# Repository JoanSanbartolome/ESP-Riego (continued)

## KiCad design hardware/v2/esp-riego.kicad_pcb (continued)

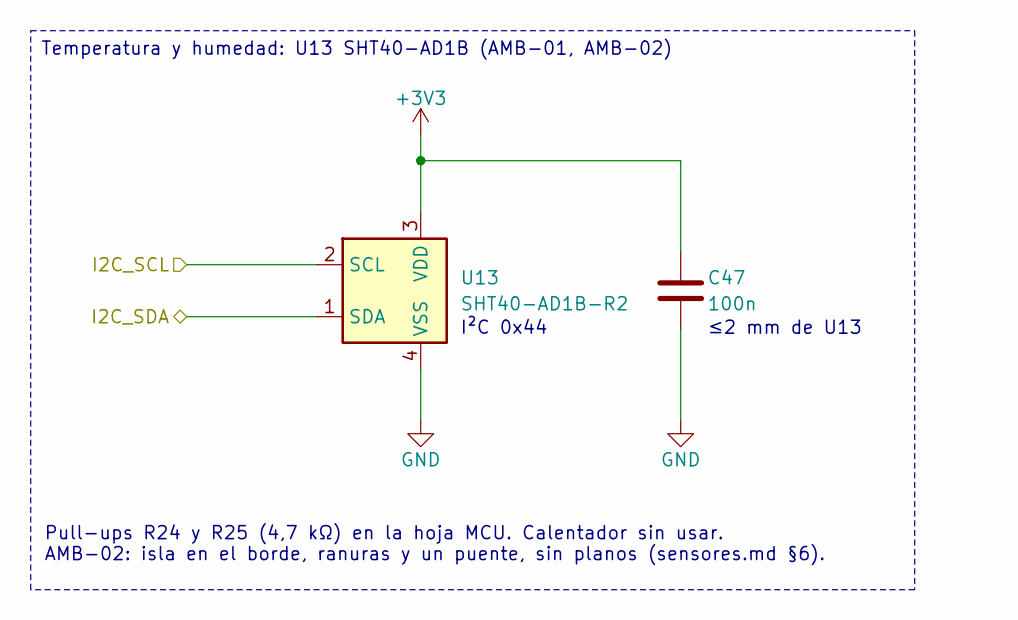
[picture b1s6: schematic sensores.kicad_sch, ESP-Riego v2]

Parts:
C47: 100n; C_0603_1608Metric; MPN CC0603KRX7R9BB104; LCSC Part# C14663
U13: SHT40-AD1B-R2; Sensirion_DFN-4_1.5x1.5mm_P0.8mm_SHT4x_NoCentralPad; MPN SHT40-AD1B-R2; LCSC Part# C2909890

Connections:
+3V3: C47.1, U13.3 (VDD); also elsewhere on the board
/I2C_SCL: U13.2 (SCL); also elsewhere on the board
/I2C_SDA: U13.1 (SDA); also elsewhere on the board
GND: C47.2, U13.4 (VSS); also elsewhere on the board

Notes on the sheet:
I²C 0x44
≤2 mm de U13
Pull-ups R24 y R25 (4,7 kΩ) en la hoja MCU. Calentador sin usar. AMB-02: isla en el borde, ranuras y un puente, sin planos (sensores.md §6).
Temperatura y humedad: U13 SHT40-AD1B (AMB-01, AMB-02)

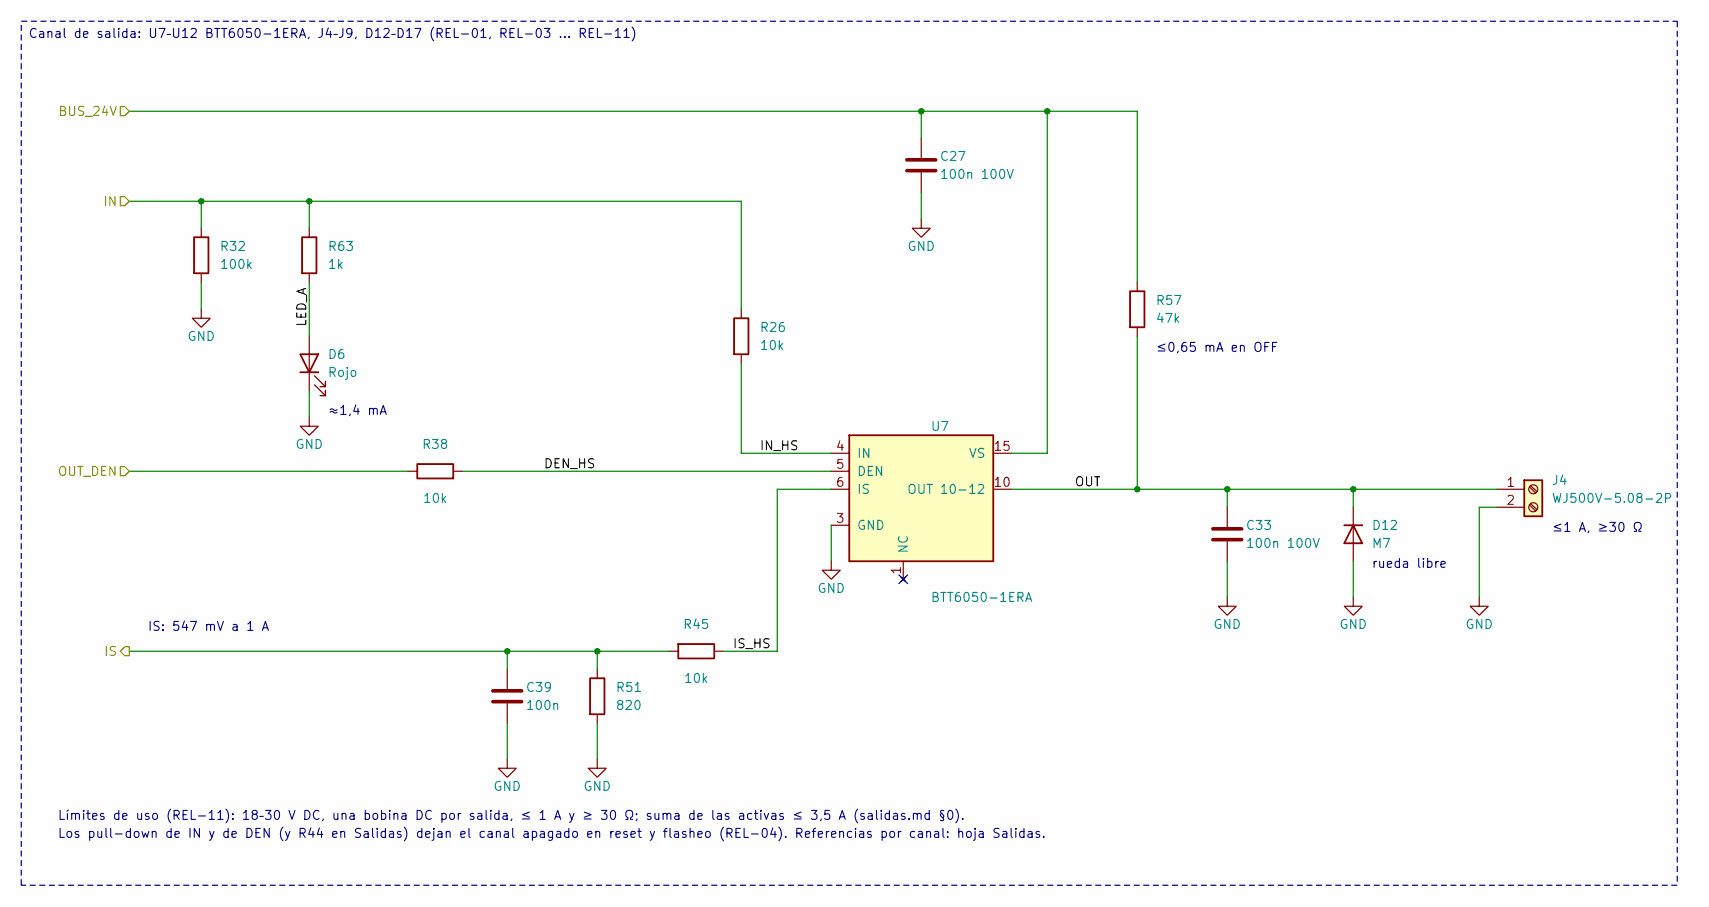
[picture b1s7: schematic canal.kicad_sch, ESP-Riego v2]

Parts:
C27, C33: 100n 100V; C_0805_2012Metric; MPN CL21B104KCFNNNE; LCSC Part# C28233
C39: 100n; C_0603_1608Metric; MPN CC0603KRX7R9BB104; LCSC Part# C14663
D6: Rojo; LED_0603_1608Metric; MPN KT-0603R; LCSC Part# C2286
D12: M7; D_SMA; MPN M7; LCSC Part# C95872
J4: WJ500V-5.08-2P; TerminalBlock_Kangnex_WJ500V-5.08-2P_1x02_P5.08mm_Horizontal; MPN WJ500V-5.08-2P; LCSC Part# C8465
R26, R38: 10k; R_0603_1608Metric; MPN 0603WAF1002T5E; LCSC Part# C25804
R32: 100k; R_0603_1608Metric; MPN 0603WAF1003T5E; LCSC Part# C25803
R45: 10k; R_1206_3216Metric; MPN 1206W4F1002T5E; LCSC Part# C17902
R51: 820; R_0603_1608Metric; MPN 0603WAF8200T5E; LCSC Part# C23253
R57: 47k; R_0805_2012Metric; MPN 0805W8F4702T5E; LCSC Part# C17713
R63: 1k; R_0603_1608Metric; MPN 0603WAF1001T5E; LCSC Part# C21190
U7: BTT6050-1ERA; Infineon_PG-TDSO-14_8.65x3.9mm_P1.27mm_EP2.65x6.4mm; MPN BTT6050-1ERA; LCSC Part# C534868

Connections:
/BUS_24V: C27.1, R57.1, U7.15 (VS); also elsewhere on the board
/IN1: R26.1, R32.1, R63.1; also elsewhere on the board
/IS1: C39.1, R45.2, R51.1; also elsewhere on the board
/OUT_DEN: R38.1; also elsewhere on the board
/Salidas/Canal1/DEN_HS: R38.2, U7.5 (DEN)
/Salidas/Canal1/IN_HS: R26.2, U7.4 (IN)
/Salidas/Canal1/IS_HS: R45.1, U7.6 (IS)
/Salidas/Canal1/LED_A: D6.2 (A), R63.2
/Salidas/Canal1/OUT: C33.1, D12.1 (K), J4.1, R57.2, U7.10 (OUT 10-12), U7.11 (OUT 10-12), U7.12 (OUT 10-12)
GND: C27.2, C33.2, C39.2, D6.1 (K), D12.2 (A), J4.2, R32.2, R51.2, U7.3 (GND); also elsewhere on the board

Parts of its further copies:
C28, C29, C30, C31, C32, C34, C35, C36, C37, C38: 100n 100V; C_0805_2012Metric; MPN CL21B104KCFNNNE; LCSC Part# C28233
C40, C41, C42, C43, C44: 100n; C_0603_1608Metric; MPN CC0603KRX7R9BB104; LCSC Part# C14663
D7, D8, D9, D10, D11: Rojo; LED_0603_1608Metric; MPN KT-0603R; LCSC Part# C2286
D13, D14, D15, D16, D17: M7; D_SMA; MPN M7; LCSC Part# C95872
J5, J6, J7, J8, J9: WJ500V-5.08-2P; TerminalBlock_Kangnex_WJ500V-5.08-2P_1x02_P5.08mm_Horizontal; MPN WJ500V-5.08-2P; LCSC Part# C8465
R27, R28, R29, R30, R31, R39, R40, R41, R42, R43: 10k; R_0603_1608Metric; MPN 0603WAF1002T5E; LCSC Part# C25804
R33, R34, R35, R36, R37: 100k; R_0603_1608Metric; MPN 0603WAF1003T5E; LCSC Part# C25803
R46, R47, R48, R49, R50: 10k; R_1206_3216Metric; MPN 1206W4F1002T5E; LCSC Part# C17902
R52, R53, R54, R55, R56: 820; R_0603_1608Metric; MPN 0603WAF8200T5E; LCSC Part# C23253
R58, R59, R60, R61, R62: 47k; R_0805_2012Metric; MPN 0805W8F4702T5E; LCSC Part# C17713
R64, R65, R66, R67, R68: 1k; R_0603_1608Metric; MPN 0603WAF1001T5E; LCSC Part# C21190
U8, U9, U10, U11, U12: BTT6050-1ERA; Infineon_PG-TDSO-14_8.65x3.9mm_P1.27mm_EP2.65x6.4mm; MPN BTT6050-1ERA; LCSC Part# C534868

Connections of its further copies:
/BUS_24V: C28.1, C29.1, C30.1, C31.1, C32.1, R58.1, R59.1, R60.1, R61.1, R62.1, U8.15 (VS), U9.15 (VS), U10.15 (VS), U11.15 (VS), U12.15 (VS); also elsewhere on the board
/IN2: R27.1, R33.1, R64.1; also elsewhere on the board
/IN3: R28.1, R34.1, R65.1; also elsewhere on the board
/IN4: R29.1, R35.1, R66.1; also elsewhere on the board
/IN5: R30.1, R36.1, R67.1; also elsewhere on the board
/IN6: R31.1, R37.1, R68.1; also elsewhere on the board
/IS2: C40.1, R46.2, R52.1; also elsewhere on the board
/IS3: C41.1, R47.2, R53.1; also elsewhere on the board
/IS4: C42.1, R48.2, R54.1; also elsewhere on the board
/IS5: C43.1, R49.2, R55.1; also elsewhere on the board
/IS6: C44.1, R50.2, R56.1; also elsewhere on the board
/OUT_DEN: R39.1, R40.1, R41.1, R42.1, R43.1; also elsewhere on the board
/Salidas/Canal2/DEN_HS: R39.2, U8.5 (DEN)
/Salidas/Canal2/IN_HS: R27.2, U8.4 (IN)
/Salidas/Canal2/IS_HS: R46.1, U8.6 (IS)
/Salidas/Canal2/LED_A: D7.2 (A), R64.2
/Salidas/Canal2/OUT: C34.1, D13.1 (K), J5.1, R58.2, U8.10 (OUT 10-12), U8.11 (OUT 10-12), U8.12 (OUT 10-12)
/Salidas/Canal3/DEN_HS: R40.2, U9.5 (DEN)
/Salidas/Canal3/IN_HS: R28.2, U9.4 (IN)
/Salidas/Canal3/IS_HS: R47.1, U9.6 (IS)
/Salidas/Canal3/LED_A: D8.2 (A), R65.2
/Salidas/Canal3/OUT: C35.1, D14.1 (K), J6.1, R59.2, U9.10 (OUT 10-12), U9.11 (OUT 10-12), U9.12 (OUT 10-12)
/Salidas/Canal4/DEN_HS: R41.2, U10.5 (DEN)
/Salidas/Canal4/IN_HS: R29.2, U10.4 (IN)
/Salidas/Canal4/IS_HS: R48.1, U10.6 (IS)
/Salidas/Canal4/LED_A: D9.2 (A), R66.2
/Salidas/Canal4/OUT: C36.1, D15.1 (K), J7.1, R60.2, U10.10 (OUT 10-12), U10.11 (OUT 10-12), U10.12 (OUT 10-12)
/Salidas/Canal5/DEN_HS: R42.2, U11.5 (DEN)
/Salidas/Canal5/IN_HS: R30.2, U11.4 (IN)
/Salidas/Canal5/IS_HS: R49.1, U11.6 (IS)
/Salidas/Canal5/LED_A: D10.2 (A), R67.2
/Salidas/Canal5/OUT: C37.1, D16.1 (K), J8.1, R61.2, U11.10 (OUT 10-12), U11.11 (OUT 10-12), U11.12 (OUT 10-12)
/Salidas/Canal6/DEN_HS: R43.2, U12.5 (DEN)
/Salidas/Canal6/IN_HS: R31.2, U12.4 (IN)
/Salidas/Canal6/IS_HS: R50.1, U12.6 (IS)
/Salidas/Canal6/LED_A: D11.2 (A), R68.2
/Salidas/Canal6/OUT: C38.1, D17.1 (K), J9.1, R62.2, U12.10 (OUT 10-12), U12.11 (OUT 10-12), U12.12 (OUT 10-12)
GND: C28.2, C29.2, C30.2, C31.2, C32.2, C34.2, C35.2, C36.2, C37.2, C38.2, C40.2, C41.2, C42.2, C43.2, C44.2, D7.1 (K), D8.1 (K), D9.1 (K), D10.1 (K), D11.1 (K), D13.2 (A), D14.2 (A), D15.2 (A), D16.2 (A), D17.2 (A), J5.2, J6.2, J7.2, J8.2, J9.2, R33.2, R34.2, R35.2, R36.2, R37.2, R52.2, R53.2, R54.2, R55.2, R56.2, U8.3 (GND), U9.3 (GND), U10.3 (GND), U11.3 (GND), U12.3 (GND); also elsewhere on the board

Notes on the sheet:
≈1,4 mA
≤0,65 mA en OFF
rueda libre
≤1 A, ≥30 Ω
IS: 547 mV a 1 A
Límites de uso (REL-11): 18–30 V DC, una bobina DC por salida, ≤ 1 A y ≥ 30 Ω; suma de las activas ≤ 3,5 A (salidas.md §0).
Los pull-down de IN y de DEN (y R44 en Salidas) dejan el canal apagado en reset y flasheo (REL-04). Referencias por canal: hoja Salidas.
Canal de salida: U7–U12 BTT6050-1ERA, J4–J9, D12–D17 (REL-01, REL-03 … REL-11)

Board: 2 copper layers, 197 parts (0 on the bottom side), 101 nets, no tracks yet.

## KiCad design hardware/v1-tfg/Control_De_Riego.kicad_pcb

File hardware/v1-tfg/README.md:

# v1-tfg — proyecto del TFG en formato KiCad 10

Copia de la v1 (`Control_De_Riego`) del TFG de Joan San Bartolomé Ferri. **El diseño no se ha tocado**: solo se han cambiado las rutas de librería, la hoja de dibujo, los modelos 3D y el formato de archivo (SPEC-0009). Los hallazgos H1–H12 de `docs/01-analisis-v1.md` siguen presentes.

## Origen

`C:\Users\josan\proyectos\TFG\KiCad_PCB\Control_De_Riego` (carpeta de trabajo, igual que `PCB_FINAL.rar`) y `C:\Users\josan\proyectos\TFG\Llibreries_Kicad`. Solo se leyó del TFG; su huella (`gestion/tfg-manifiesto.json`) sigue intacta.

## Qué se copió

- Proyecto: `Control_De_Riego.kicad_pro`, `.kicad_sch` (raíz), `allimentacion`, `conectores`, `modulo_reles`, `wemos_s2mini` (`.kicad_sch`) y `Control_De_Riego.kicad_pcb`.
- `referencia/Panel_Control.kicad_sch`: hoja fuera de la jerarquía (H9), solo como referencia. Está guardada también en formato KiCad 10.
- Librerías propias en `../libraries/` con los mismos nicknames que las tablas originales (ver abajo).

No se copió: `Control_De_Riego-backups/`, `fp-info-cache`, `.kicad_prl`, `.step` del proyecto, `untitled.kicad_sch` (duplicado del Wemos) ni los `.rar`.

## Librerías (`../libraries/`)

| Nickname | Tipo | Archivo | Origen |
|---|---|---|---|
| `PS2705-1-F3-A`, `BC817-25-7-F`, `1548129`, `PRT-10811` | símbolos | `<nick>.kicad_sym` | `.lib` + `.dcm` de la librería del TFG, convertidos con `kicad-cli sym upgrade` |
| `Wemos s2 mini` | símbolo | `Wemos s2 mini.kicad_sym` | JSON de EasyEDA (`SCHLIB_WEMOS-S2-MINI-…json`) convertido tal cual con `kicad-cli sym upgrade -o` (SPEC-0010) |
| `PS2705`, `BC817-25-7`, `PRT10811`, `KiCad`, `PhoenixTerminal`, `SMMS0530-150M` | huellas | `<nick>.pretty` | `.kicad_mod` de la librería del TFG, actualizados con `kicad-cli fp upgrade` (`KiCad` = `1548129`; `SMMS0530-150M` incluye también `IND-SMD_L5.5-W5.2`) |
| `Wemos s2 mini` | huella | `Wemos s2 mini.pretty` | JSON de EasyEDA (`PCBLIB_WEMOS-S2-MINI_…json`) convertido tal cual con `kicad-cli fp upgrade -o` (SPEC-0010); no lleva modelo 3D |
| `DC-Jack` | huella | `DC-Jack.pretty/DC-IN-TH_XDJK-0051-025` | JSON de EasyEDA convertido tal cual con `kicad-cli fp upgrade -o` (SPEC-0010). Tiene 3 pads; el pad 3 es `custom` con polígono de 3,56 × 1,60 mm y taladro oblongo de 3×1 mm, equivalente a los pads 1 y 2 girados 90° (no es un artefacto). No se usa en la PCB (el jack real es `Connector_BarrelJack`) |

También `Cajetin_Kicad.kicad_wks` (hoja de dibujo) y `3d/` (`TLP185.step`, `Transistor.IGS`, `PSMT3012.STEP`, `Wemos S2 Mini V1.0.0.step`).

## Cambios de ruta

- `sym-lib-table` y `fp-lib-table`: reescritas con `${KIPRJMOD}/../libraries/...` y tipo `KiCad` (antes `Legacy` y EasyEDA, con rutas `G:/…`).
- `Control_De_Riego.kicad_pro`: `page_layout_descr_file` (dos apariciones) a `${KIPRJMOD}/../libraries/Cajetin_Kicad.kicad_wks`; `export… svg` (ruta `C:/Users/josan/Desktop/…`, último directorio de exportación) vaciado.
- `Control_De_Riego.kicad_pcb`: 10 modelos 3D con ruta `G:/…` a `${KIPRJMOD}/../libraries/3d/<archivo>` (4× TLP185, 4× Transistor, 1× PSMT3012, 1× Wemos); 43 modelos `${KICAD9_3DMODEL_DIR}` a `${KICAD10_3DMODEL_DIR}` (normalización a la variable de KiCad 10; la antigua también resuelve, así que el cambio es inocuo).
- Modelos 3D: 42 de los 53 modelos de la PCB apuntan a un `.wrl`, y KiCad 10.0.6 no instala ningún `.wrl` (solo `.step`), así que esos modelos no se ven en el visor 3D ni en el STEP (`Could not add 3D model`). Viene de la v1; se corrige en la copia de trabajo de la v2 (`.wrl` a `.step`).
- Esquemas y PCB: `kicad-cli sch|pcb upgrade --force` (esquema `20260306`, PCB `20260206`).

## Verificación

`python herramientas/verificar.py hardware/v1-tfg`:

| | Antes (copia sin migrar) | Después |
|---|---|---|
| ERC | 1 (`pin_to_pin`) | 1 (`pin_to_pin`) |
| DRC | 1 error `starved_thermal`, 39 `lib_footprint_mismatch`, 0 sin conectar | 1 error `starved_thermal`, 39 `lib_footprint_mismatch`, 0 sin conectar (40 en total, como antes) |
| Paridad | 77 (61 `LCSC Part#`, 10 `net_conflict`, 6 huellas) | 77 (igual) |

Tras SPEC-0010 el DRC coincide con la copia sin migrar: la huella `Wemos s2 mini` de la librería es la conversión del JSON de EasyEDA, igual que en el TFG, y vuelve a no coincidir con la copia de U1 en la PCB (`lib_footprint_mismatch`). Con la copia embebida en la PCB (SPEC-0009) el DRC era 39. Netlist (61 componentes, 70 redes), posiciones, pistas (262), vías (36) y zonas (3) son idénticas antes y después. Detalle en `gestion/logs/SPEC-0009/01-jr-conformidad.md`.

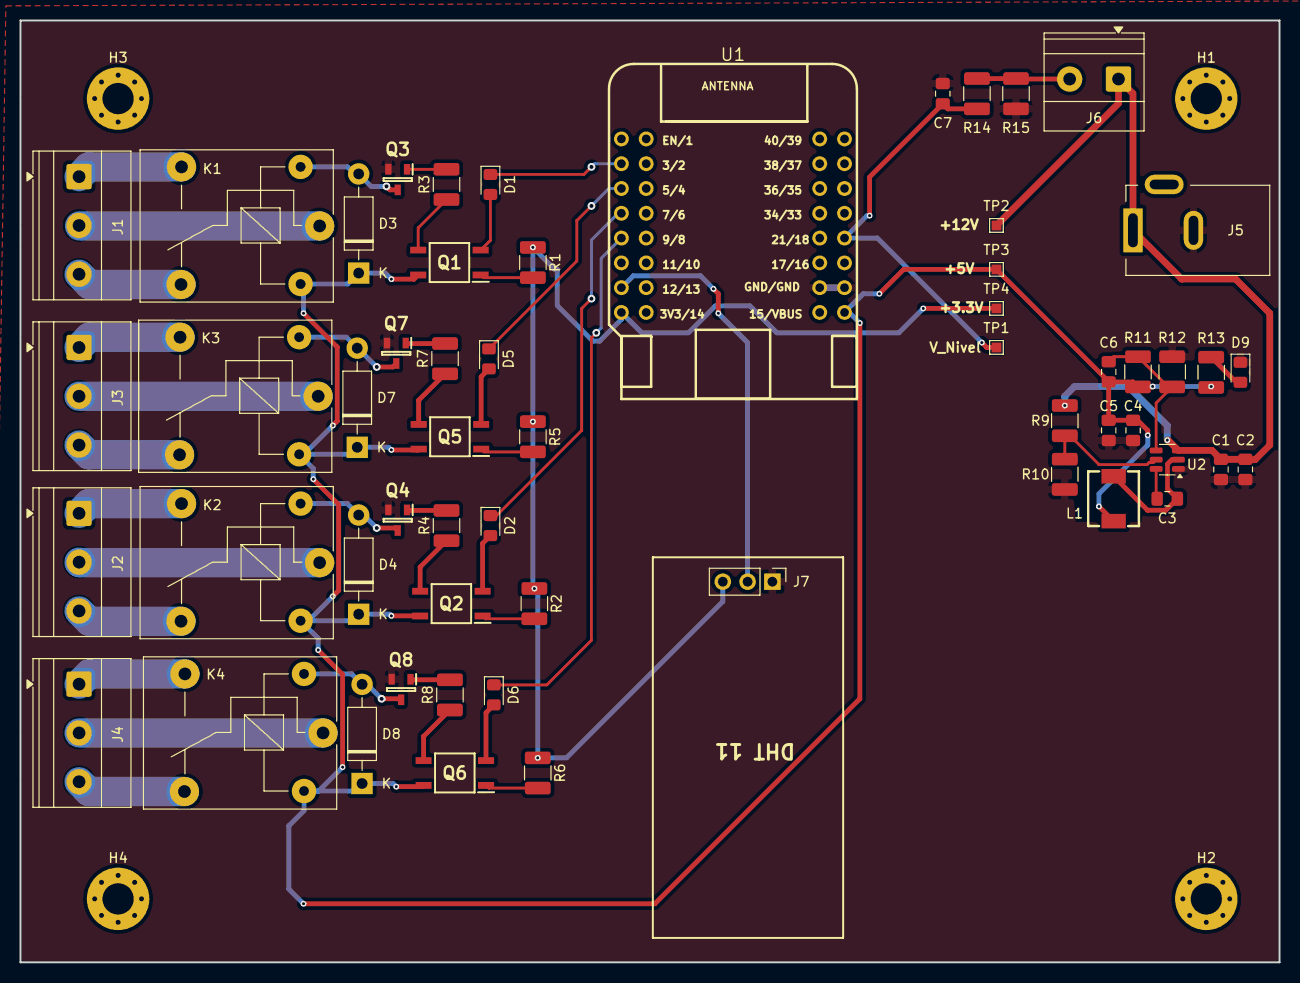
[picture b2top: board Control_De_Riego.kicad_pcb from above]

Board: 2 copper layers, 129.0 x 96.5 mm, 61 parts (0 on the bottom side), 48 nets.

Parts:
C1: 10uF; C_0805_2012Metric_Pad1.18x1.45mm_HandSolder
C2, C3, C7: 100nF; C_0805_2012Metric_Pad1.18x1.45mm_HandSolder
C4, C5: 22uF; C_0805_2012Metric_Pad1.18x1.45mm_HandSolder
C6: 68pF; C_0805_2012Metric_Pad1.18x1.45mm_HandSolder
D1, D2, D5, D6: Red; LED_0805_2012Metric_Pad1.15x1.40mm_HandSolder
D3, D4, D7, D8: 1N4007; D_DO-41_SOD81_P10.16mm_Horizontal
D9: Green; LED_0805_2012Metric_Pad1.15x1.40mm_HandSolder
H1, H2, H3, H4: MountingHole; MountingHole_3.2mm_M3_Pad_Via
J1: Conector Rele 1; TerminalBlock_Phoenix_MKDS-1,5-3_1x03_P5.00mm_Horizontal
J2: Conector Rele 3; TerminalBlock_Phoenix_MKDS-1,5-3_1x03_P5.00mm_Horizontal
J3: Conector Rele 2; TerminalBlock_Phoenix_MKDS-1,5-3_1x03_P5.00mm_Horizontal
J4: Conector Rele 4; TerminalBlock_Phoenix_MKDS-1,5-3_1x03_P5.00mm_Horizontal
J5: DC Jack; BarrelJack_Kycon_KLDX-0202-xC_Horizontal
J6: Conn_01x02; TerminalBlock_Phoenix_MKDS-1,5-2_1x02_P5.00mm_Horizontal
J7: Conn_01x03; PinHeader_1x03_P2.54mm_Vertical
K1, K2, K3, K4: SANYOU_SRD_Form_C; Relay_SPDT_SANYOU_SRD_Series_Form_C
L1: 22uH; IND-SMD_L5.5-W5.2
Q1, Q2, Q5, Q6: PS2705-1-F3-A; SOP254P700X230-4N
Q3, Q4, Q7, Q8: BC817-25-7-F; SOT96P240X110-3N
R1, R2, R5, R6: 50; R_1210_3225Metric_Pad1.30x2.65mm_HandSolder
R3, R4, R7, R8: 1k; R_1210_3225Metric_Pad1.30x2.65mm_HandSolder
R9, R14: 270k; R_1210_3225Metric_Pad1.30x2.65mm_HandSolder
R10: 33k; R_1210_3225Metric_Pad1.30x2.65mm_HandSolder
R11: 100k; R_1210_3225Metric_Pad1.30x2.65mm_HandSolder
R12: 13k; R_1210_3225Metric_Pad1.30x2.65mm_HandSolder
R13: 180; R_1210_3225Metric_Pad1.30x2.65mm_HandSolder
R15: 150; R_1210_3225Metric_Pad1.30x2.65mm_HandSolder
TP1, TP2, TP3, TP4: TestPoint; TestPoint_Pad_1.0x1.0mm
U1: WEMOS-S2-MINI (ESP32-S2FN4R2); WEMOS-S2-MINI
U2: TPS54202DDC; SOT-23-6

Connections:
+3.3V: J7.3, R1.1, R2.1, R5.1, R6.1, TP4.1, U1.15 (3V3)
+5V: C4.1, C5.1, C6.1, D3.1 (K), D4.1 (K), D7.1 (K), D8.1 (K), K1.5, K2.5, K3.5, K4.5, L1.2, Q1.4 (C), Q2.4 (C), Q5.4 (C), Q6.4 (C), R11.1, R13.1, TP3.1, U1.18 (VBUS)
+12V: C1.1, C2.1, J5.1, J6.1, R9.2, TP2.1, U2.3 (VIN)
/Modulo_reles/IN_REL1: J1.2, K1.1
/Modulo_reles/IN_REL2: J3.2, K3.1
/Modulo_reles/IN_REL3: J2.2, K2.1
/Modulo_reles/IN_REL4: J4.2, K4.1
/Modulo_reles/NC_REL1: J1.3, K1.4
/Modulo_reles/NC_REL2: J3.3, K3.4
/Modulo_reles/NC_REL3: J2.3, K2.4
/Modulo_reles/NC_REL4: J4.3, K4.4
/Modulo_reles/NO_REL1: J1.1, K1.3
/Modulo_reles/NO_REL2: J3.1, K3.3
/Modulo_reles/NO_REL3: J2.1, K2.3
/Modulo_reles/NO_REL4: J4.1, K4.3
GND: C1.2, C2.2, C4.2, C5.2, C7.2, D9.1 (K), J5.2, J7.1, Q3.2, Q4.2, Q7.2, Q8.2, R10.2, R12.1, R15.2, U1.19 (GND), U1.20 (GND), U2.1 (GND)
unnamed: D1.2 (A), Q1.2 (KA)
unnamed: D2.2 (A), Q2.2 (KA)
unnamed: D3.2 (A), K1.2, Q3.3
unnamed: D4.2 (A), K2.2, Q4.3
unnamed: D5.2 (A), Q5.2 (KA)
unnamed: D6.2 (A), Q6.2 (KA)
unnamed: D7.2 (A), K3.2, Q7.3
unnamed: D8.2 (A), K4.2, Q8.3
unnamed: D9.2 (A), R13.2
unnamed: J6.2, R14.2, R15.1
unnamed: Q1.1 (AK), R1.2
unnamed: Q1.3 (E), R3.1
unnamed: Q2.1 (AK), R2.2
unnamed: Q2.3 (E), R4.1
unnamed: Q3.1, R3.2
unnamed: Q4.1, R4.2
unnamed: Q5.1 (AK), R5.2
unnamed: Q5.3 (E), R7.1
unnamed: Q6.1 (AK), R6.2
unnamed: Q6.3 (E), R8.1
unnamed: Q7.1, R7.2
unnamed: Q8.1, R8.2
unnamed: C3.1, U2.6 (BOOT)
unnamed: R9.1, R10.1, U2.5 (EN)
unnamed: C6.2, R11.2, R12.2, U2.4 (FB)
unnamed: C3.2, L1.1, U2.2 (SW)
REL1: D1.1 (K), U1.3 (IO3)
REL2: D5.1 (K), U1.5 (IO5)
REL3: D2.1 (K), U1.7 (IO7)
REL4: D6.1 (K), U1.9 (IO9)
TH_Data: J7.2, U1.13 (IO12)
V_Level: C7.1, R14.1, TP1.1, U1.24 (IO18)

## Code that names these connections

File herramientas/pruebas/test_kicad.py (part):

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        mayúsculas, minúsculas con descendente, cifras, varias líneas, justificaciones y etiquetas giradas."""
        casos = [("text", "TLV1117LV33DCYR", 0, "left bottom"), ("text", "TPS26632RGER", 0, "right bottom"),
                 ("text", "Ag 4.7u 100V", 0, ""), ("text", "ABC\\nDEF\\nGHI", 0, "left top"),
                 ("text", "≤3 mm de U5-2", 0, "left"), ("label", "LED_STATUS", 0, "left bottom"),
                 ("label", "VIN_PROT", 180, "right bottom"), ("label", "I2C_SDA", 90, "left bottom"),
                 ("label", "BTN_INT", 270, "right bottom")]
        cuerpo = ""
        for k, (tipo, t, ang, j) in enumerate(casos):
            jj = f" (justify {j})" if j else ""
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                p["conexion"] = "L:" + p["nombre"]
        desc.write_text(json.dumps(d), encoding="utf-8")
        sensores = next(h for h in d["hojas"] if h["nombre"] == "Sensores")
        self.assertIn({"nombre": "I2C_SCL", "forma": "input", "lado": "R", "y": 93.98, "conexion": "L:I2C_SCL"}, sensores["pines"])
        _comun.escribir(raiz, _comun.leer(raiz).replace('(pin "I2C_SCL" input', '(pin "I2C_SCL" output', 1))  # la descripción manda
        codigo, salida, error = correr("hoja", "raiz", desc, "--proyecto", proy, "-o", raiz)
        self.assertEqual(codigo, 0, salida + error)
        self.assertIn("5 hojas, 54 pines de hoja, 54 etiquetas o NC · avisos 0", salida)
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    def test_netlist_plan(self):
        """hoja.py netlist --plan: cada red del plan, con exactamente esos pines; NC; sección; entradas sin interpretar."""
        doc = TMP / "plan.md"
        doc.write_text("# Doc\n\n## Anexo A. Plan\n\n| Red | Pines |\n|---|---|\n| `/I2C_SDA` = {U5-34, R24-2, U13-1, U18-15} | |\n"
                       "- Internas: ILIM_5V {U14-5, R69-1}; NC {U18-11, U18-12}; BTN1…BTN6 {SWn-1, U18 P0…P5}.\n\n"
                       "## Otra\n\n- X = {U5-34}\n", encoding="utf-8")
        codigo, salida, error = correr("hoja", "netlist", BASE / "v2", "--plan", doc, "--seccion", "Anexo A")
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        self.assertIn("(Anexo A): 3 redes, 8 pines; 0 diferencias; 1 entradas sin interpretar", salida)
        codigo, salida, _ = correr("hoja", "netlist", BASE / "v2", "--plan", doc)
        self.assertEqual(codigo, 1)
        self.assertIn("X: no está en la netlist (sus pines están en /I2C_SDA)", salida)
        plan, ignoradas = hoja.leer_plan(doc.read_text(encoding="utf-8"), "anexo a")
        self.assertEqual(plan[0], ("/I2C_SDA", [("U5", "34"), ("R24", "2"), ("U13", "1"), ("U18", "15")]))
        self.assertEqual(len(ignoradas), 1)
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                         "/Conectores/ILIM_5V": {("U14", "5"), ("R69", "1")}, "/Otra/ILIM_5V": {("R1", "1")},
                         "unconnected-(U18-P6-Pad11)": {("U18", "11")}, "GND": {("U18", "12"), ("U13", "1")}}}
        dif = hoja.comparar_plan(net, plan)
        self.assertEqual(dif, ["/I2C_SDA: falta U13-1 (está en «GND»)", "/I2C_SDA: pines de más R99-1", "NC: U18-12 está en «GND»"])
        codigo, _, error = correr("hoja", "netlist", BASE / "v2", BASE / "v2", "--plan", doc)
        self.assertEqual(codigo, 2)
        self.assertIn("un solo proyecto", error)
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        self.falla("esquema.cruces", "sensores.kicad_sch: cable (134.62, 101.6)–(149.86, 101.6) cruza U13",
                   "«SOLAPE» (nota)")
        self.anadir(sens, '\t(label "SUELTA" (at 50.8 50.8 0) (effects (font (size 1.27 1.27))) (uuid "m3"))\n'
                          '\t(hierarchical_label "I2C_SDA" (shape bidirectional) (at 125.73 104.14 180)'
                          ' (effects (font (size 1.27 1.27)) (justify right)) (uuid "m4"))')
        self.falla("esquema.sueltas", "label «SUELTA» suelta en (50.8, 50.8)")
        self.falla("esquema.etiquetas", "«I2C_SDA» 2 veces en el recuadro «Temperatura y humedad")
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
